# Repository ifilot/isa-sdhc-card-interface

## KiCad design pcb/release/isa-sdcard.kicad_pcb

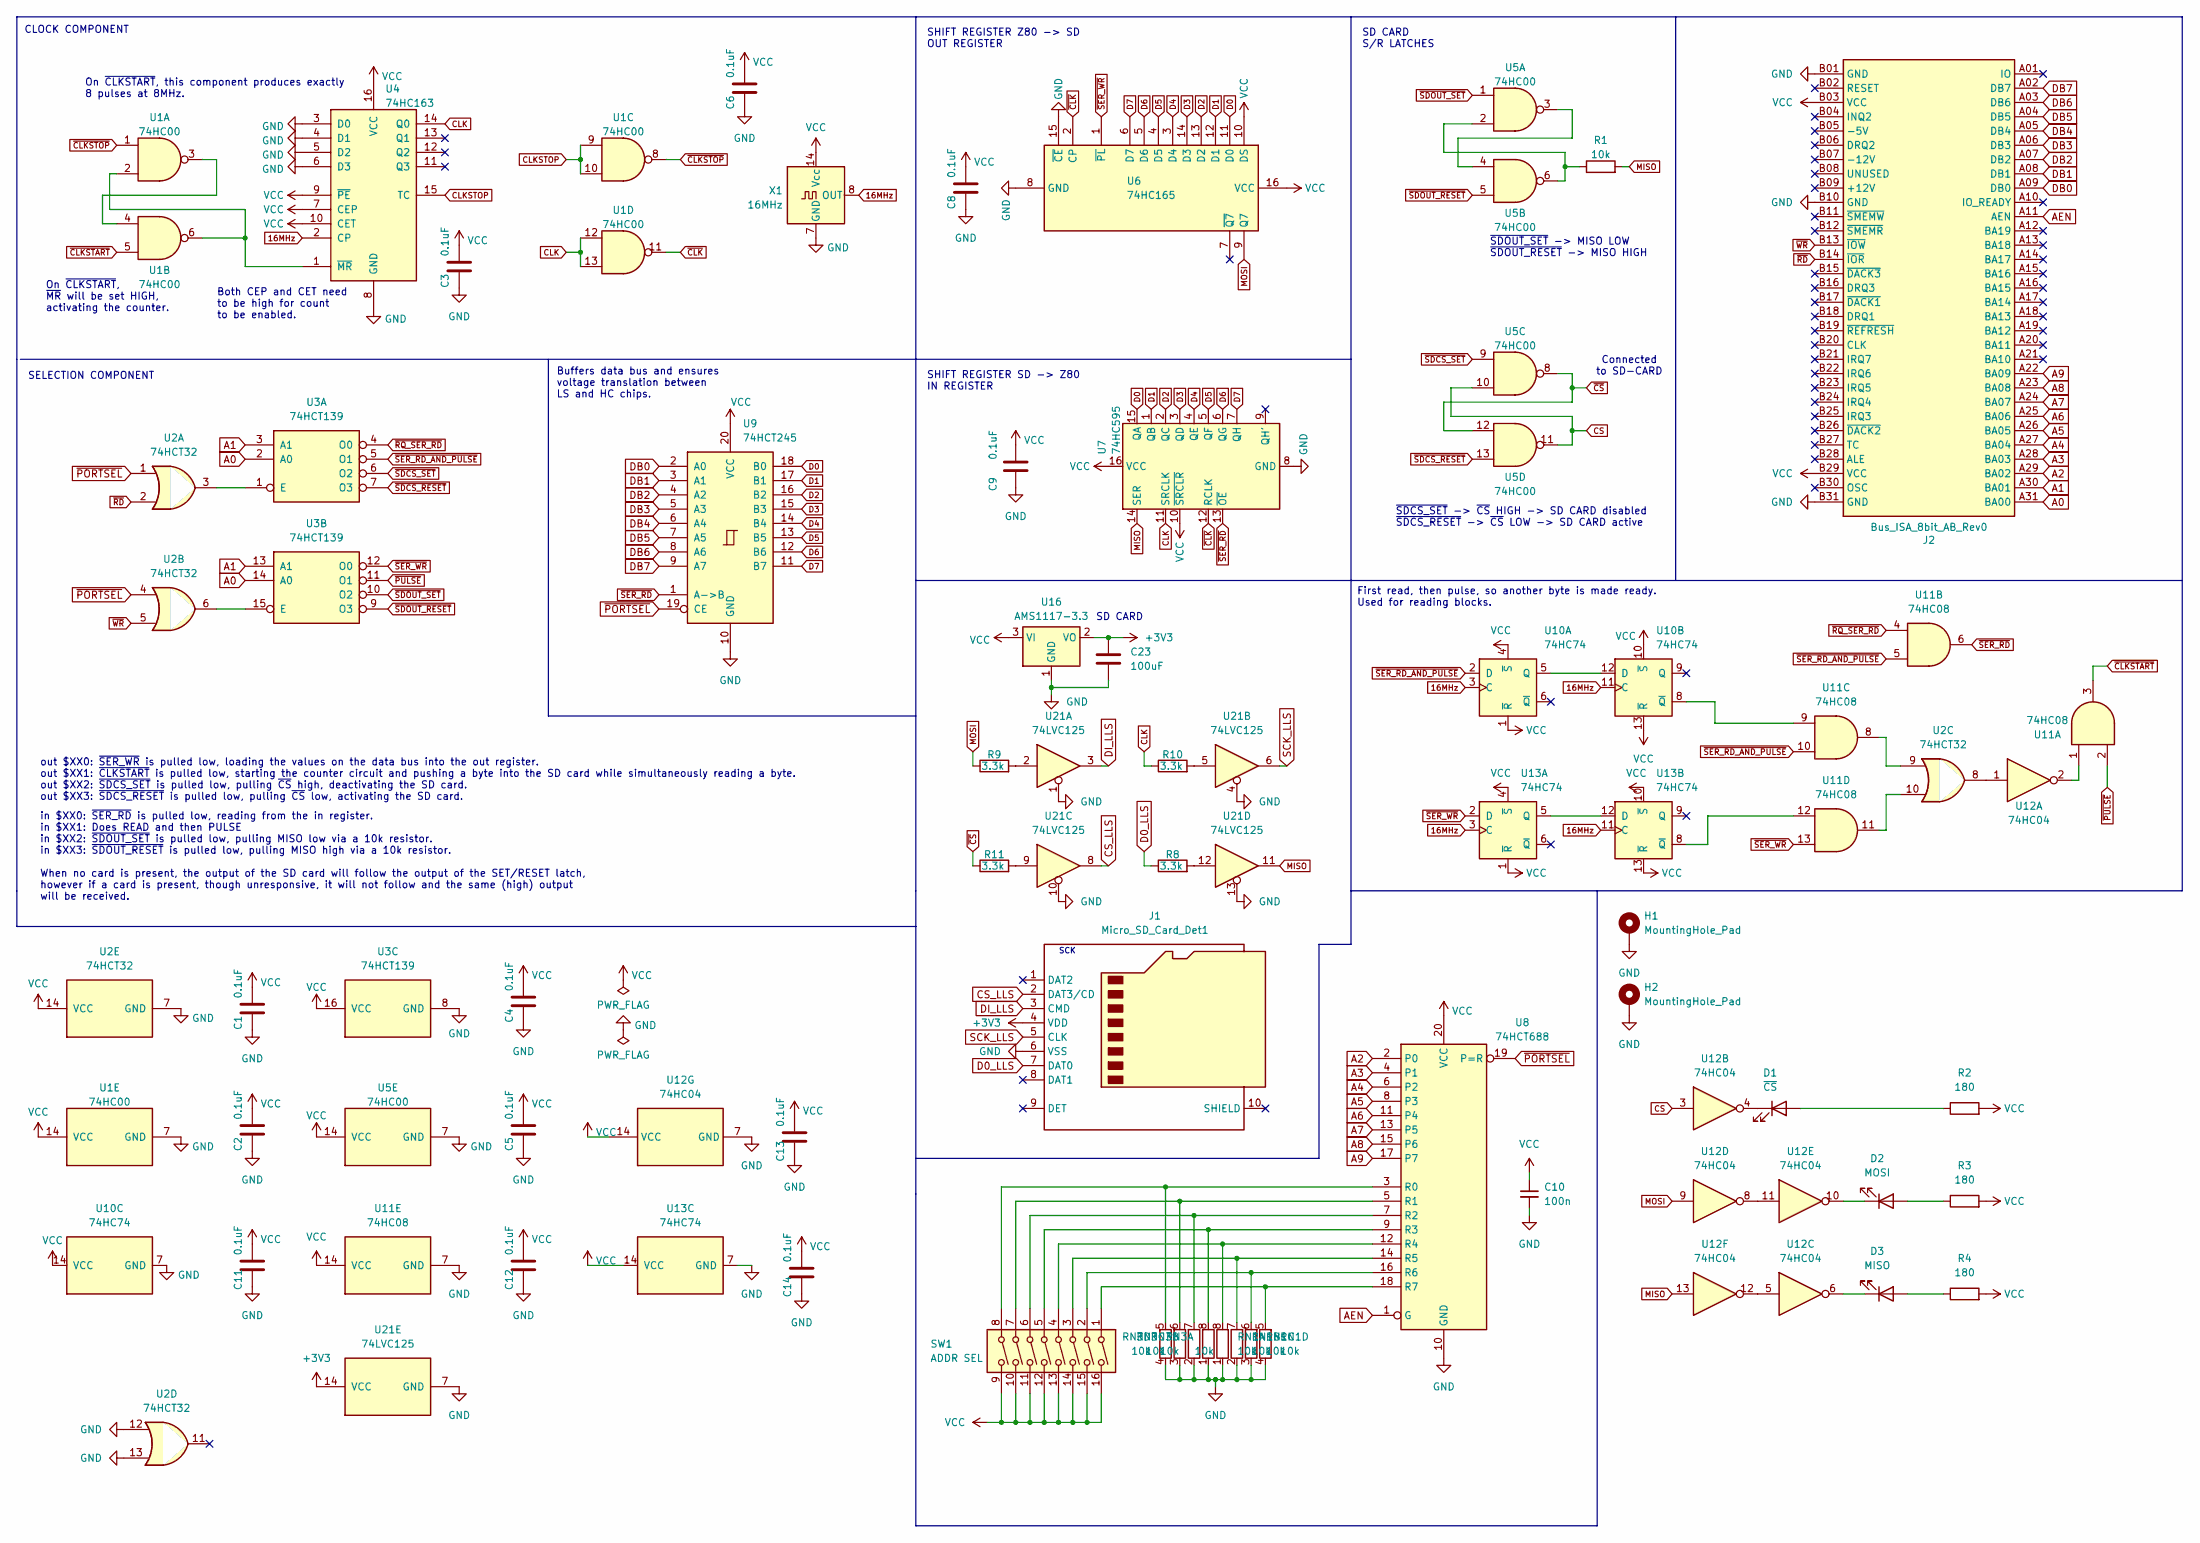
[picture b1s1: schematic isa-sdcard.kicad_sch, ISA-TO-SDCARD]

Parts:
C1, C2, C3, C4, C5, C6, C8, C9, C11, C12, C13, C14: 0.1uF; C_0805_2012Metric; LCSC Part # C126469
C10: 100n; C_0805_2012Metric
C23: 100uF; C_1206_3216Metric_Pad1.33x1.80mm_HandSolder; LCSC Part # C309030
D1: ~{CS}; LED_0805_2012Metric
D2: MOSI; LED_0805_2012Metric
D3: MISO; LED_0805_2012Metric
H1, H2: MountingHole_Pad; MountingHole_3.2mm_M3_DIN965_Pad_TopBottom
J1: Micro_SD_Card_Det1; CONN9_MSD-1_CUD; LCSC Part # C381082
J2: Bus_ISA_8bit_AB_Rev0; ISA_CARD_EDGE_CONNECTOR_8BIT_Rev1
R1: 10k; R_0805_2012Metric; LCSC Part # C5159708
R2, R3, R4: 180; R_0805_2012Metric
R8, R9, R10, R11: 3.3k; R_0805_2012Metric_Pad1.20x1.40mm_HandSolder; LCSC Part # C407459
RN1, RN3: 10k; R_Array_Convex_4x0612
SW1: ADDR SEL; SW_DIP_SPSTx08_Slide_9.78x22.5mm_W7.62mm_P2.54mm
U1, U5: 74HC00; SOIC-14_3.9x8.7mm_P1.27mm; LCSC Part # C699445
U2: 74HCT32; SOIC-14_3.9x8.7mm_P1.27mm
U3: 74HCT139; SOIC-16_3.9x9.9mm_P1.27mm
U4: 74HC163; SOIC-16_3.9x9.9mm_P1.27mm; LCSC Part # C338758
U6: 74HC165; SOIC-16_3.9x9.9mm_P1.27mm; LCSC Part # C5613
U7: 74HC595; SOIC-16_3.9x9.9mm_P1.27mm; LCSC Part # C5947
U8: 74HCT688; SOIC-20W_7.5x12.8mm_P1.27mm
U9: 74HCT245; SOIC-20W_7.5x12.8mm_P1.27mm
U10, U13: 74HC74; SOIC-14_3.9x8.7mm_P1.27mm
U11: 74HC08; SOIC-14_3.9x8.7mm_P1.27mm
U12: 74HC04; SOIC-14_3.9x8.7mm_P1.27mm
U16: AMS1117-3.3; SOT-223-3_TabPin2; LCSC Part # C5346136
U21: 74LVC125; TSSOP-14_4.4x5mm_P0.65mm
X1: 16MHz; Oscillator_DIP-14

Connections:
16MHz: U4.2 (CP), U10.3 (C), U10.11 (C), U13.3 (C), U13.11 (C), X1.8 (OUT)
+3V3: C23.1, J1.4 (VDD), U16.2 (VO), U21.14 (VCC)
A0: J2.A31 (BA00), U3.2 (A0), U3.14 (A0)
A1: J2.A30 (BA01), U3.3 (A1), U3.13 (A1)
A2: J2.A29 (BA02), U8.2 (P0)
A3: J2.A28 (BA03), U8.4 (P1)
A4: J2.A27 (BA04), U8.6 (P2)
A5: J2.A26 (BA05), U8.8 (P3)
A6: J2.A25 (BA06), U8.11 (P4)
A7: J2.A24 (BA07), U8.13 (P5)
A8: J2.A23 (BA08), U8.15 (P6)
A9: J2.A22 (BA09), U8.17 (P7)
AEN: J2.A11 (AEN), U8.1 (G)
CLK: R10.1, U1.12, U1.13, U4.14 (Q0), U7.11 (SRCLK)
CLKSTOP: U1.9, U1.10, U4.15 (TC)
CS: U5.10, U5.11, U12.3
CS_LLS: J1.2 (DAT3/CD), U21.8
D0: U6.11 (D0), U7.15 (QA), U9.18 (B0)
D0_LLS: J1.7 (DAT0), R8.1
D1: U6.12 (D1), U7.1 (QB), U9.17 (B1)
D2: U6.13 (D2), U7.2 (QC), U9.16 (B2)
D3: U6.14 (D3), U7.3 (QD), U9.15 (B3)
D4: U6.3 (D4), U7.4 (QE), U9.14 (B4)
D5: U6.4 (D5), U7.5 (QF), U9.13 (B5)
D6: U6.5 (D6), U7.6 (QG), U9.12 (B6)
D7: U6.6 (D7), U7.7 (QH), U9.11 (B7)
DB0: J2.A09 (DB0), U9.2 (A0)
DB1: J2.A08 (DB1), U9.3 (A1)
DB2: J2.A07 (DB2), U9.4 (A2)
DB3: J2.A06 (DB3), U9.5 (A3)
DB4: J2.A05 (DB4), U9.6 (A4)
DB5: J2.A04 (DB5), U9.7 (A5)
DB6: J2.A03 (DB6), U9.8 (A6)
DB7: J2.A02 (DB7), U9.9 (A7)
DI_LLS: J1.3 (CMD), U21.3
GND: C1.1, C2.1, C3.1, C4.1, C5.1, C6.1, C8.1, C9.1, C10.2, C11.1, C12.1, C13.1, C14.1, C23.2, H1.1, H2.1, J1.6 (VSS), J2.B01 (GND), J2.B10 (GND), J2.B31 (GND), RN1.1 (R1.1), RN1.2 (R2.1), RN1.3 (R3.1), RN1.4 (R4.1), RN3.1 (R1.1), RN3.2 (R2.1), RN3.3 (R3.1), RN3.4 (R4.1), U1.7 (GND), U2.7 (GND), U2.12, U2.13, U3.8 (GND), U4.3 (D0), U4.4 (D1), U4.5 (D2), U4.6 (D3), U4.8 (GND), U5.7 (GND), U6.8 (GND), U6.15 (~CE), U7.8 (GND), U8.10 (GND), U9.10 (GND), U10.7 (GND), U11.7 (GND), U12.7 (GND), U13.7 (GND), U16.1 (GND), U21.1, U21.4, U21.7 (GND), U21.10, U21.13, X1.7 (GND)
MISO: R1.2, U7.14 (SER), U12.13, U21.11
MOSI: R9.1, U6.9 (Q7), U12.9
unnamed: D1.2 (A), R2.1
unnamed: D1.1 (K), U12.4
unnamed: D2.2 (A), R3.1
unnamed: D2.1 (K), U12.10
unnamed: D3.2 (A), R4.1
unnamed: D3.1 (K), U12.6
unnamed: R1.1, U5.2, U5.6
unnamed: R8.2, U21.12
unnamed: R9.2, U21.2
unnamed: R10.2, U21.5
unnamed: R11.2, U21.9
unnamed: RN1.8 (R1.2), SW1.4, U8.12 (R4)
unnamed: RN1.7 (R2.2), SW1.3, U8.14 (R5)
unnamed: RN1.6 (R3.2), SW1.2, U8.16 (R6)
unnamed: RN1.5 (R4.2), SW1.1, U8.18 (R7)
unnamed: RN3.8 (R1.2), SW1.5, U8.9 (R3)
unnamed: RN3.7 (R2.2), SW1.6, U8.7 (R2)
unnamed: RN3.6 (R3.2), SW1.7, U8.5 (R1)
unnamed: RN3.5 (R4.2), SW1.8, U8.3 (R0)
unnamed: U1.3, U1.4
unnamed: U2.3, U3.1 (E)
unnamed: U2.6, U3.15 (E)
unnamed: U1.2, U1.6, U4.1 (~MR)
unnamed: U5.3, U5.4
unnamed: U10.5 (Q), U10.12 (D)
unnamed: U10.8 (~Q), U11.9
unnamed: U11.1, U12.2
unnamed: U2.9, U11.8
unnamed: U2.10, U11.11
unnamed: U2.8, U12.1
unnamed: U12.8, U12.11
unnamed: U12.5, U12.12
unnamed: U13.5 (Q), U13.12 (D)
unnamed: U11.12, U13.8 (~Q)
SCK_LLS: J1.5 (CLK), U21.6
VCC: C1.2, C2.2, C3.2, C4.2, C5.2, C6.2, C8.2, C9.2, C10.1, C11.2, C12.2, C13.2, C14.2, J2.B03 (VCC), J2.B29 (VCC), R2.2, R3.2, R4.2, SW1.9, SW1.10, SW1.11, SW1.12, SW1.13, SW1.14, SW1.15, SW1.16, U1.14 (VCC), U2.14 (VCC), U3.16 (VCC), U4.7 (CEP), U4.9 (~PE), U4.10 (CET), U4.16 (VCC), U5.14 (VCC), U6.10 (DS), U6.16 (VCC), U7.10 (~SRCLR), U7.16 (VCC), U8.20 (VCC), U9.20 (VCC), U10.1 (~R), U10.4 (~S), U10.10 (~S), U10.13 (~R), U10.14 (VCC), U11.14 (VCC), U12.14 (VCC), U13.1 (~R), U13.4 (~S), U13.10 (~S), U13.13 (~R), U13.14 (VCC), U16.3 (VI), X1.14 (Vcc)
~CLKSTART: U1.5, U11.3
~CLKSTOP: U1.1, U1.8
~CLK: U1.11, U6.2 (CP), U7.12 (RCLK)
~CS: R11.1, U5.8, U5.12
~PORTSEL: U2.1, U2.4, U8.19 (P=R), U9.19 (CE)
~PULSE: U3.11 (O1), U11.2
~RD: J2.B14 (~IOR), U2.2
~RQ_SER_RD: U3.4 (O0), U11.4
~SDCS_RESET: U3.7 (O3), U5.13
~SDCS_SET: U3.6 (O2), U5.9
~SDOUT_RESET: U3.9 (O3), U5.5
~SDOUT_SET: U3.10 (O2), U5.1
~SER_RD_AND_PULSE: U3.5 (O1), U10.2 (D), U11.5, U11.10
~SER_RD: U7.13 (~OE), U9.1 (A->B), U11.6
~SER_WR: U3.12 (O0), U6.1 (~PL), U11.13, U13.2 (D)
~WR: J2.B13 (~IOW), U2.5

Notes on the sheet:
First read, then pulse, so another byte is made ready. Used for reading blocks.
SHIFT REGISTER SD -> Z80 IN REGISTER
SD CARD S/R LATCHES
out $XX0: ~{SER_WR} is pulled low, loading the values on the data bus into the out register. out $XX1: ~{CLKSTART} is pulled low, starting the counter circuit and pushing a byte into the SD card while simultaneously reading a byte. out $XX2: ~{SDCS_SET} is pulled low, pulling ~{CS} high, deactivati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
On ~{CLKSTART}, this component produces exactly 8 pulses at 8MHz.
SCK
On ~{CLKSTART}, ~{MR} will be set HIGH, activating the counter.
in $XX0: ~{SER_RD} is pulled low, reading from the in register. in $XX1: Does READ and then PULSE in $XX2: ~{SDOUT_SET} is pulled low, pulling MISO low via a 10k resistor. in $XX3: ~{SDOUT_RESET} is pulled low, pulling MISO high via a 10k resistor. When no card is present, the output of the SD card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
Connected to SD-CARD
~{SDOUT_SET} -> MISO LOW ~{SDOUT_RESET} -> MISO HIGH
~{SDCS_SET} -> ~{CS} HIGH -> SD CARD disabled ~{SDCS_RESET} -> ~{CS} LOW -> SD CARD active
SELECTION COMPONENT
CLOCK COMPONENT
SD CARD
Buffers data bus and ensures voltage translation between LS and HC chips.
Both CEP and CET need to be high for count to be enabled.
SHIFT REGISTER Z80 -> SD OUT REGISTER

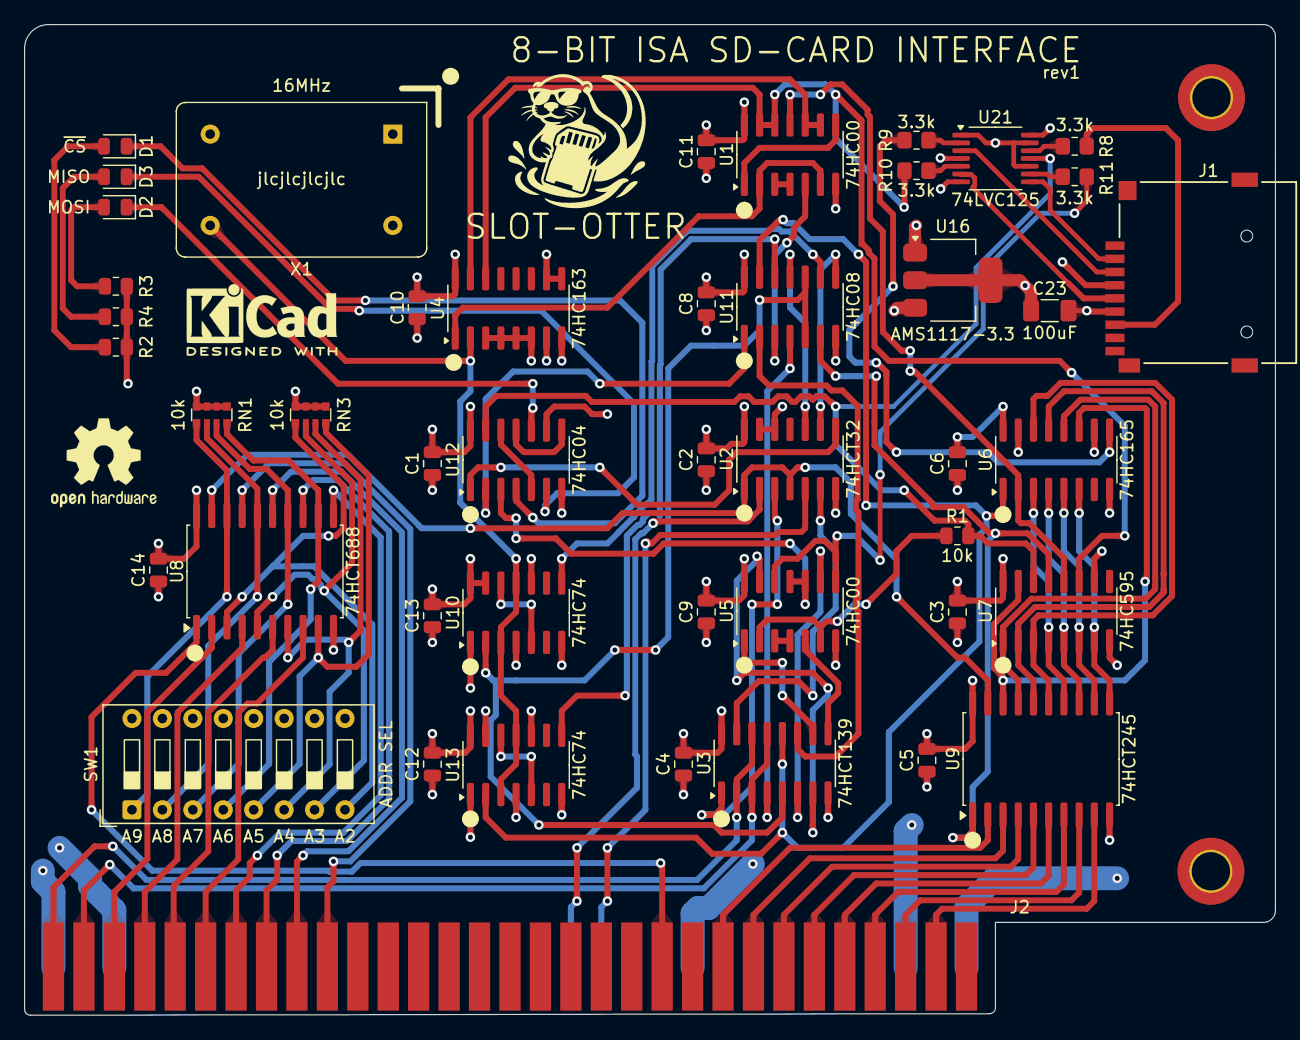
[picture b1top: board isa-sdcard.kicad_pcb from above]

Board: 4 copper layers, 104.4 x 82.7 mm, 48 parts (0 on the bottom side), 90 nets.

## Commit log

2025-08-17 Revising schematics and layout
2025-08-20 Revising design
2025-08-24 Revising lay-out
2025-09-07 Revising PCB and adding source code
2025-09-07 Leveraging some routines to assembly
2025-09-07 Adding helper and polishing assembly routines for SD interfacing
2025-09-10 Updating software
2025-09-12 Expanding PCB and adding reading directory to firmware
2025-09-13 Implementing simple SD card navigation
2025-09-13 Polishing file viewer
2025-09-14 Adding immediate pulse after rwrite and optional pulse after read
2025-09-19 Expanding navigation and implementing file transfer
2025-09-20 Copying all files from a folder
2025-09-20 Polishing interface
2025-09-20 Patching bug for large files and putting version in separate header file
2025-09-21 Adding logo
2025-09-28 Revising prototype, updating software and adding bracket
2025-09-28 Fixing software for SDHC cards
2025-09-28 Adding SD test routines
2025-09-28 Adding PCB variant
2025-10-16 Fixing CS bug in code, adding logos to PCB
